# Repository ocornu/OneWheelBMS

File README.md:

# OneWheelBMS
Open source BMS for OneWheel v1/plus

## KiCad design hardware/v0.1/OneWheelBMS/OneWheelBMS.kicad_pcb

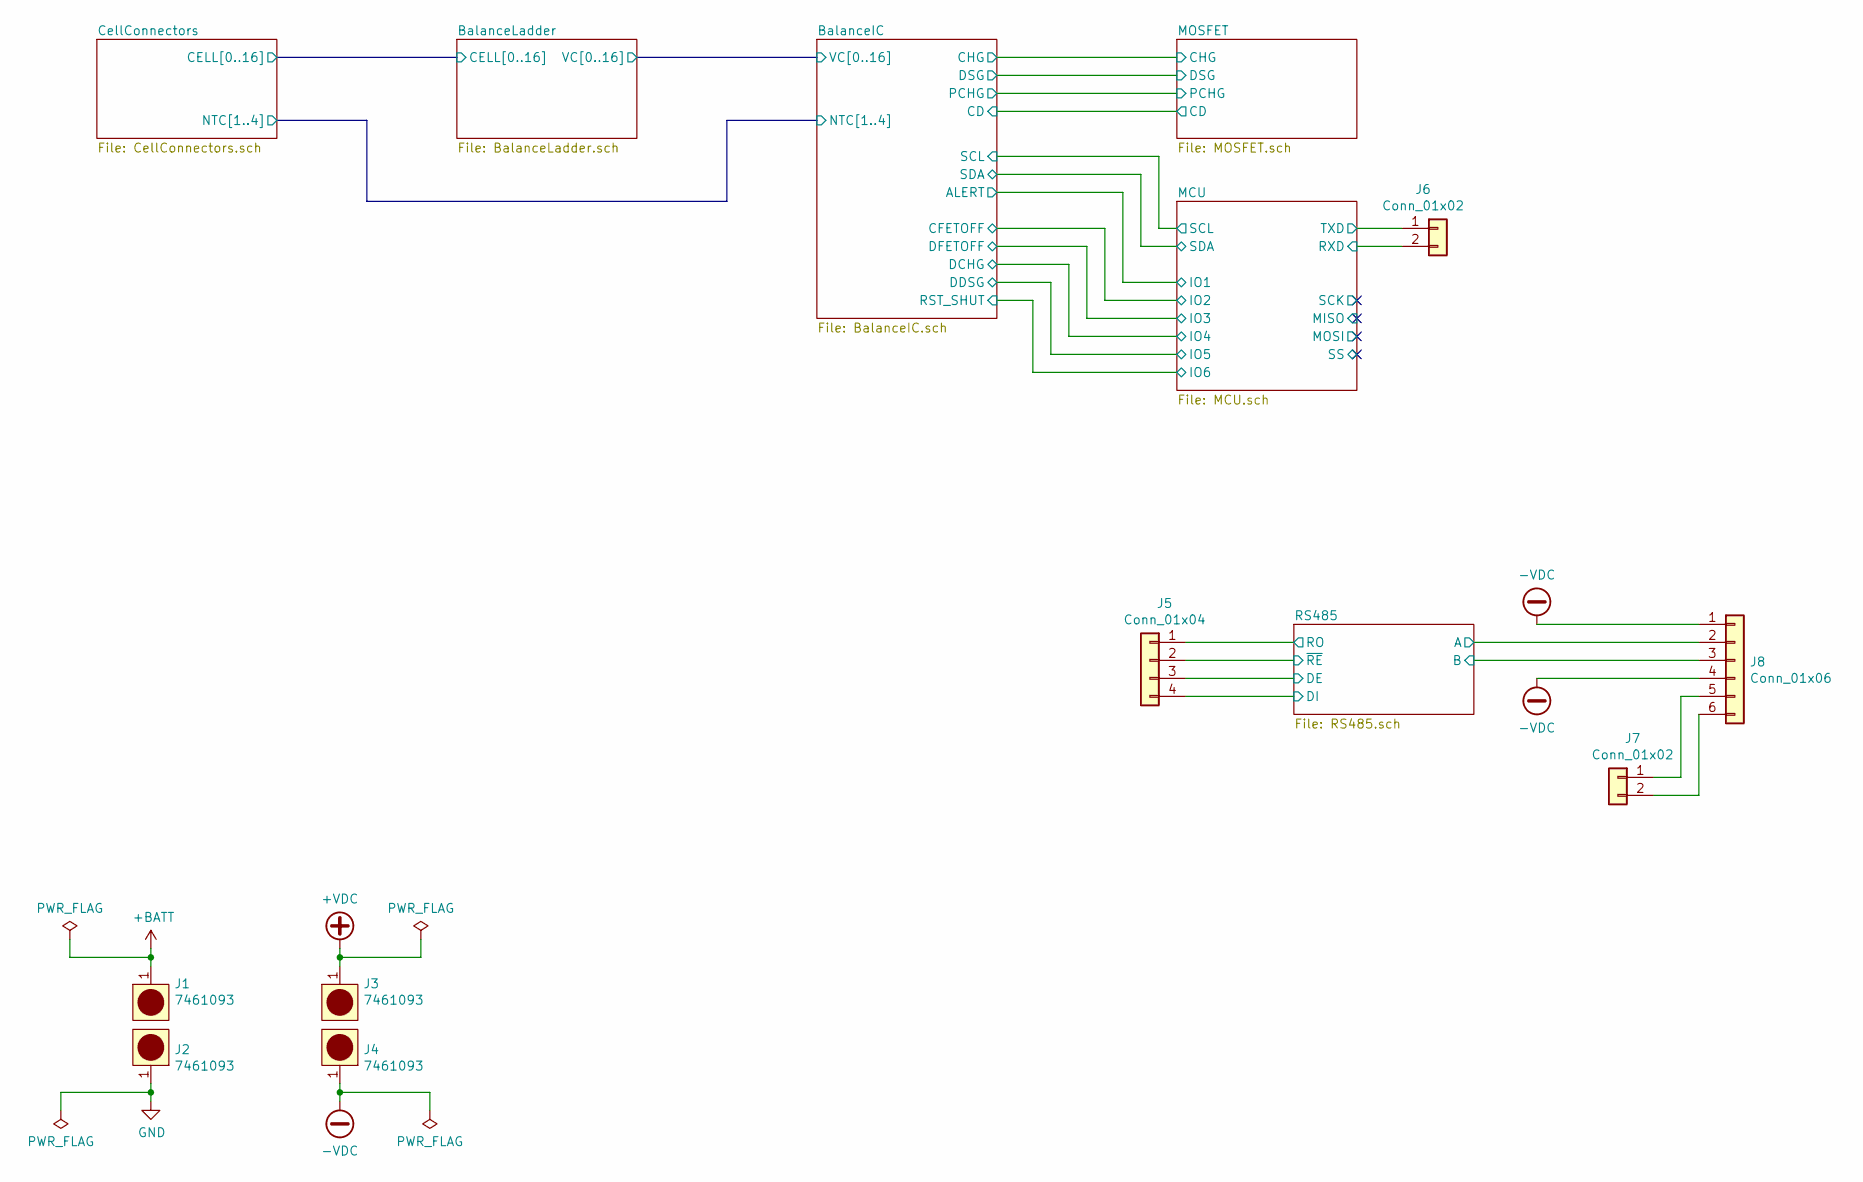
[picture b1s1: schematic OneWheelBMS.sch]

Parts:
J1, J2, J3, J4: 7461093
J5: Conn_01x04; PinHeader_1x04_P2.54mm_Vertical
J6, J7: Conn_01x02; PinHeader_1x02_P2.54mm_Vertical
J8: Conn_01x06; 5600200620

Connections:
+BATT: J1.1; also elsewhere on the board
+VDC: J3.1; also elsewhere on the board
-VDC: J4.1, J8.1, J8.4; also elsewhere on the board
/MCU/RXD: J6.2; also elsewhere on the board
/MCU/TXD: J6.1; also elsewhere on the board
/RS485/A: J8.2; also elsewhere on the board
/RS485/B: J8.3; also elsewhere on the board
/RS485/DE: J5.3; also elsewhere on the board
/RS485/DI: J5.4; also elsewhere on the board
/RS485/RO: J5.1; also elsewhere on the board
/RS485/~RE: J5.2; also elsewhere on the board
GND: J2.1; also elsewhere on the board
unnamed: J7.1, J8.5
unnamed: J7.2, J8.6

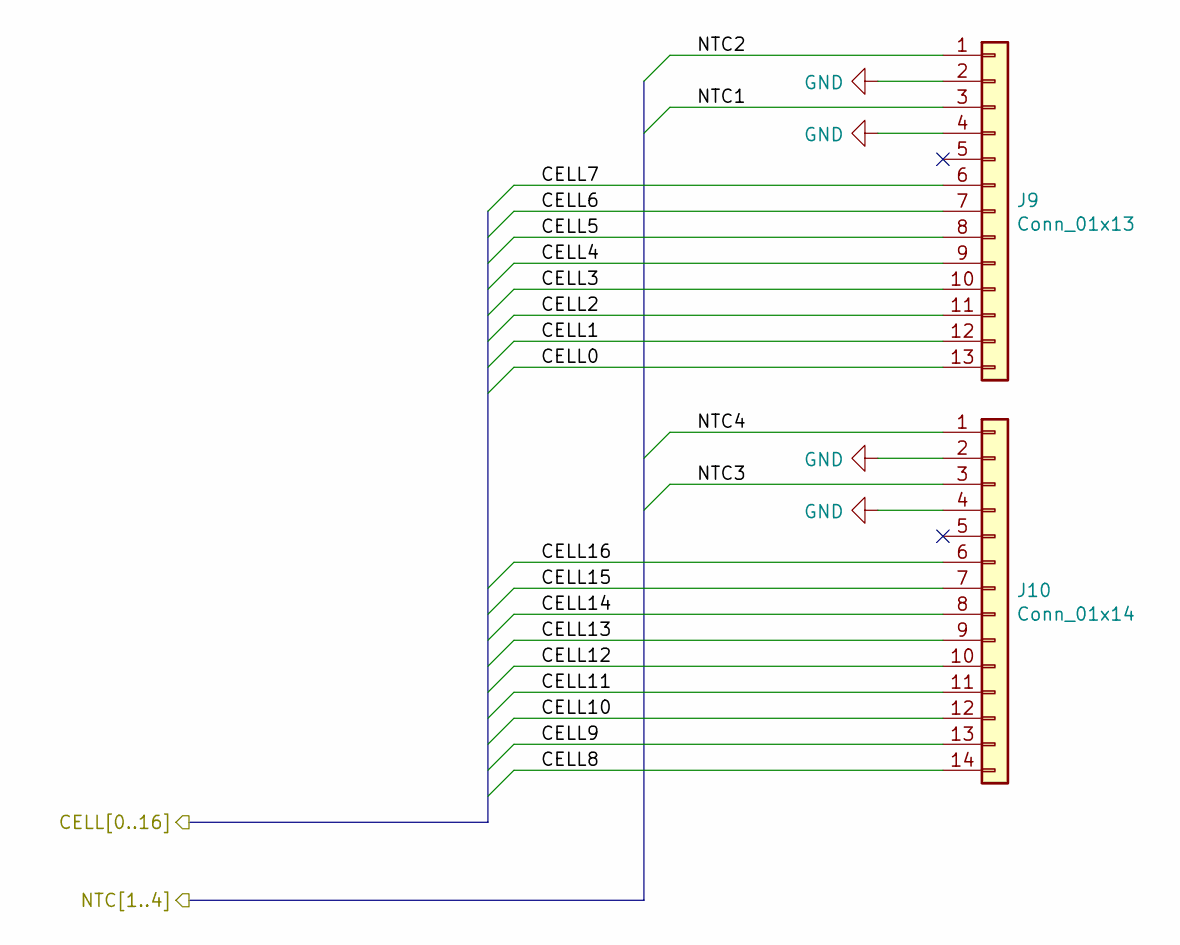
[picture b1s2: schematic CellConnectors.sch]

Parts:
J9: Conn_01x13; JST_XH_B13B-XH-A_1x13_P2.50mm_Vertical
J10: Conn_01x14; JST_XH_B14B-XH-A_1x14_P2.50mm_Vertical

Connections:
/BalanceIC/NTC1: J9.3; also elsewhere on the board
/BalanceIC/NTC2: J9.1; also elsewhere on the board
/BalanceIC/NTC3: J10.3; also elsewhere on the board
/BalanceIC/NTC4: J10.1; also elsewhere on the board
/BalanceLadder/CELL0: J9.13; also elsewhere on the board
/BalanceLadder/CELL1: J9.12; also elsewhere on the board
/BalanceLadder/CELL2: J9.11; also elsewhere on the board
/BalanceLadder/CELL3: J9.10; also elsewhere on the board
/BalanceLadder/CELL4: J9.9; also elsewhere on the board
/BalanceLadder/CELL5: J9.8; also elsewhere on the board
/BalanceLadder/CELL6: J9.7; also elsewhere on the board
/BalanceLadder/CELL7: J9.6; also elsewhere on the board
/BalanceLadder/CELL8: J10.14; also elsewhere on the board
/BalanceLadder/CELL9: J10.13; also elsewhere on the board
/BalanceLadder/CELL10: J10.12; also elsewhere on the board
/BalanceLadder/CELL11: J10.11; also elsewhere on the board
/BalanceLadder/CELL12: J10.10; also elsewhere on the board
/BalanceLadder/CELL13: J10.9; also elsewhere on the board
/BalanceLadder/CELL14: J10.8; also elsewhere on the board
/BalanceLadder/CELL15: J10.7; also elsewhere on the board
/BalanceLadder/CELL16: J10.6; also elsewhere on the board
GND: J9.2, J9.4, J10.2, J10.4; also elsewhere on the board

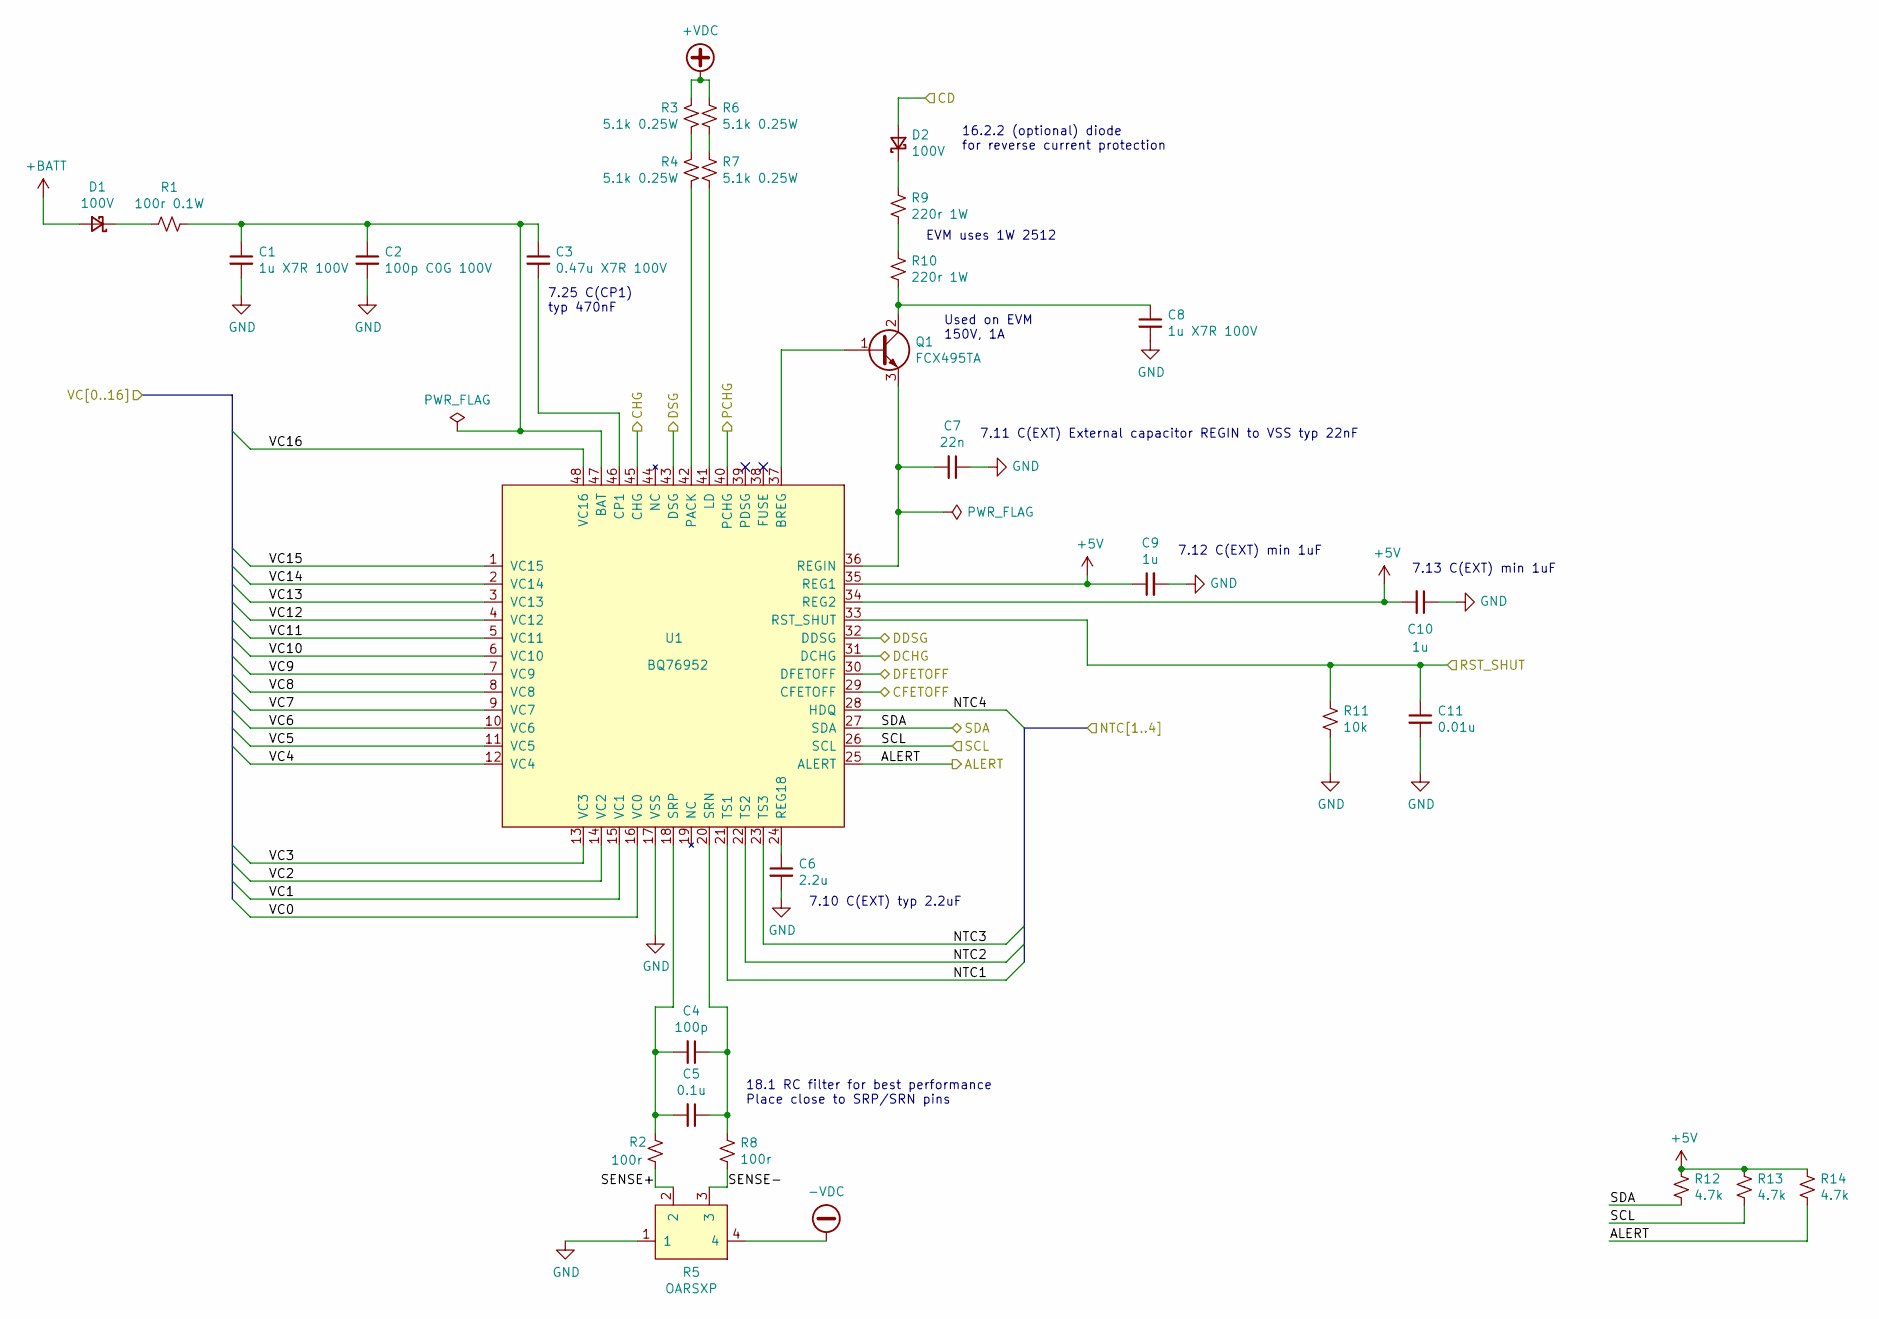
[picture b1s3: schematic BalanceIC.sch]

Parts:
C1, C8: 1u X7R 100V; C_0805_2012Metric
C2: 100p C0G 100V; C_0805_2012Metric
C3: 0.47u X7R 100V; C_0805_2012Metric
C4: 100p; C_0603_1608Metric
C5: 0.1u; C_0603_1608Metric
C6: 2.2u; C_0603_1608Metric
C7: 22n; C_0603_1608Metric
C9, C10: 1u; C_0603_1608Metric
C11: 0.01u; C_0603_1608Metric
D1, D2: 100V; D_SOD-123
Q1: FCX495TA; SOT-89-3
R1: 100r 0.1W; R_0805_2012Metric
R2, R8: 100r; R_0805_2012Metric
R3, R4, R6, R7: 5.1k 0.25W; R_0805_2012Metric
R5: OARSXP
R9, R10: 220r 1W; R_0612_1632Metric
R11: 10k; R_0603_1608Metric
R12, R13, R14: 4.7k; R_0603_1608Metric
U1: BQ76952; TQFP-48_7x7mm_P0.5mm

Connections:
+5V: C9.1, C10.2, R12.1, R13.1, R14.1, U1.34 (REG2), U1.35 (REG1); also elsewhere on the board
+BATT: D1.2 (A); also elsewhere on the board
+VDC: R3.1, R6.1; also elsewhere on the board
-VDC: R5.4; also elsewhere on the board
/BalanceIC/ALERT: R14.2, U1.25 (ALERT); also elsewhere on the board
/BalanceIC/CD: D2.2 (A); also elsewhere on the board
/BalanceIC/CFETOFF: U1.29 (CFETOFF); also elsewhere on the board
/BalanceIC/CHG: U1.45 (CHG); also elsewhere on the board
/BalanceIC/DCHG: U1.31 (DCHG); also elsewhere on the board
/BalanceIC/DDSG: U1.32 (DDSG); also elsewhere on the board
/BalanceIC/DFETOFF: U1.30 (DFETOFF); also elsewhere on the board
/BalanceIC/DSG: U1.43 (DSG); also elsewhere on the board
/BalanceIC/NTC1: U1.21 (TS1); also elsewhere on the board
/BalanceIC/NTC2: U1.22 (TS2); also elsewhere on the board
/BalanceIC/NTC3: U1.23 (TS3); also elsewhere on the board
/BalanceIC/NTC4: U1.28 (HDQ); also elsewhere on the board
/BalanceIC/PCHG: U1.40 (PCHG); also elsewhere on the board
/BalanceIC/SCL: R13.2, U1.26 (SCL); also elsewhere on the board
/BalanceIC/SDA: R12.2, U1.27 (SDA); also elsewhere on the board
/BalanceIC/SENSE+: R2.2, R5.2
/BalanceIC/SENSE-: R5.3, R8.2
/BalanceIC/VC0: U1.16 (VC0); also elsewhere on the board
/BalanceIC/VC1: U1.15 (VC1); also elsewhere on the board
/BalanceIC/VC2: U1.14 (VC2); also elsewhere on the board
/BalanceIC/VC3: U1.13 (VC3); also elsewhere on the board
/BalanceIC/VC4: U1.12 (VC4); also elsewhere on the board
/BalanceIC/VC5: U1.11 (VC5); also elsewhere on the board
/BalanceIC/VC6: U1.10 (VC6); also elsewhere on the board
/BalanceIC/VC7: U1.9 (VC7); also elsewhere on the board
/BalanceIC/VC8: U1.8 (VC8); also elsewhere on the board
/BalanceIC/VC9: U1.7 (VC9); also elsewhere on the board
/BalanceIC/VC10: U1.6 (VC10); also elsewhere on the board
/BalanceIC/VC11: U1.5 (VC11); also elsewhere on the board
/BalanceIC/VC12: U1.4 (VC12); also elsewhere on the board
/BalanceIC/VC13: U1.3 (VC13); also elsewhere on the board
/BalanceIC/VC14: U1.2 (VC14); also elsewhere on the board
/BalanceIC/VC15: U1.1 (VC15); also elsewhere on the board
/BalanceIC/VC16: U1.48 (VC16); also elsewhere on the board
/MCU/IO6: C11.1, R11.1, U1.33 (RST_SHUT); also elsewhere on the board
GND: C1.2, C2.2, C6.2, C7.1, C8.2, C9.2, C10.1, C11.2, R5.1, R11.2, U1.17 (VSS); also elsewhere on the board
unnamed: C1.1, C2.1, C3.1, R1.1, U1.47 (BAT)
unnamed: C3.2, U1.46 (CP1)
unnamed: C4.1, C5.1, R8.1, U1.20 (SRN)
unnamed: C4.2, C5.2, R2.1, U1.18 (SRP)
unnamed: C6.1, U1.24 (REG18)
unnamed: C7.2, Q1.3 (E), U1.36 (REGIN)
unnamed: C8.1, Q1.2 (C), R10.2
unnamed: D1.1 (K), R1.2
unnamed: D2.1 (K), R9.1
unnamed: Q1.1 (B), U1.37 (BREG)
unnamed: R3.2, R4.1
unnamed: R4.2, U1.42 (PACK)
unnamed: R6.2, R7.1
unnamed: R7.2, U1.41 (LD)
unnamed: R9.2, R10.1

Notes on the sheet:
7.11 C(EXT) External capacitor REGIN to VSS typ 22nF
7.12 C(EXT) min 1uF
7.13 C(EXT) min 1uF
7.10 C(EXT) typ 2.2uF
7.25 C(CP1) typ 470nF
18.1 RC filter for best performance Place close to SRP/SRN pins
16.2.2 (optional) diode for reverse current protection
Used on EVM 150V, 1A
EVM uses 1W 2512

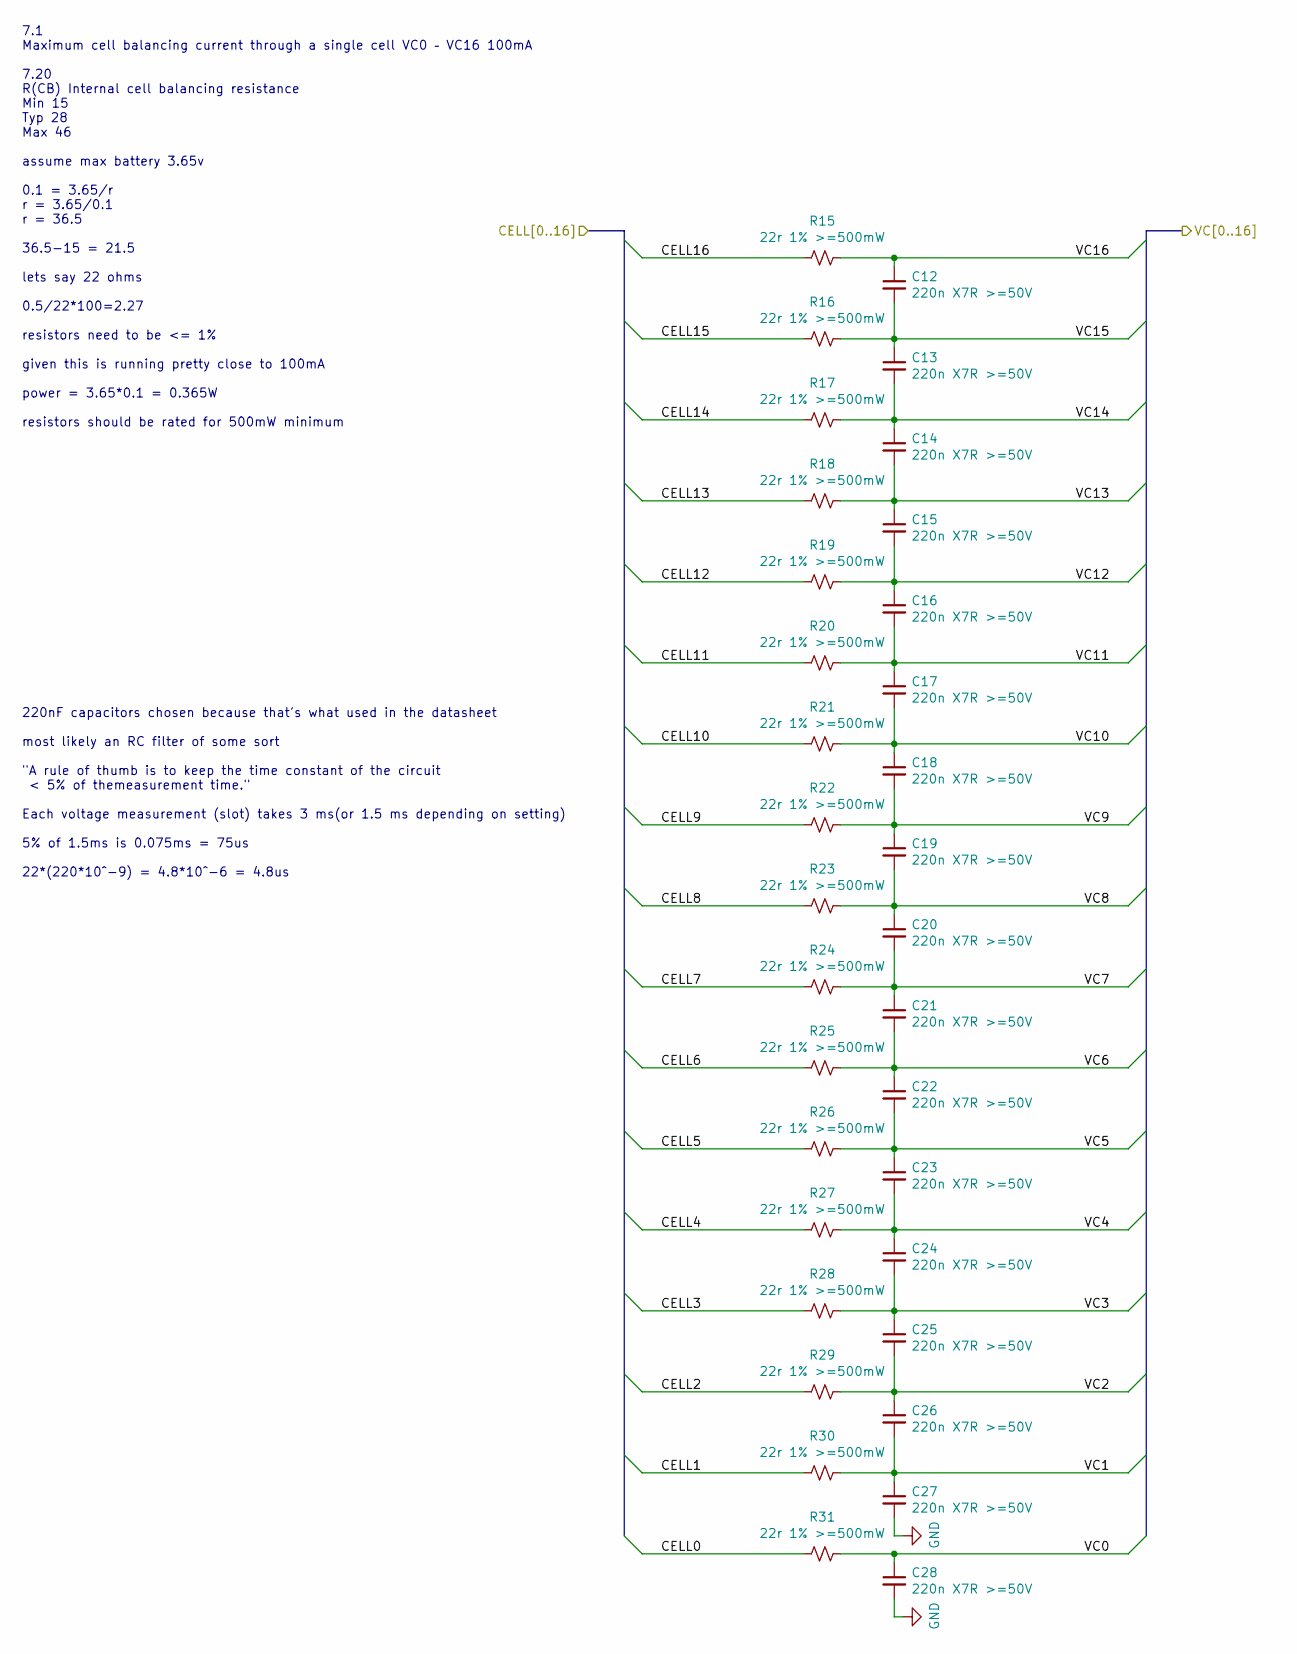
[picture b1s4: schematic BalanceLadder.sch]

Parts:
C12, C13, C14, C15, C16, C17, C18, C19, C20, C21, C22, C23, C24, C25, C26, C27, C28: 220n X7R >=50V; C_0603_1608Metric
R15, R16, R17, R18, R19, R20, R21, R22, R23, R24, R25, R26, R27, R28, R29, R30, R31: 22r 1% >=500mW; R_0612_1632Metric

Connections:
/BalanceIC/VC0: C28.1, R31.1; also elsewhere on the board
/BalanceIC/VC1: C26.2, C27.1, R30.1; also elsewhere on the board
/BalanceIC/VC2: C25.2, C26.1, R29.1; also elsewhere on the board
/BalanceIC/VC3: C24.2, C25.1, R28.1; also elsewhere on the board
/BalanceIC/VC4: C23.2, C24.1, R27.1; also elsewhere on the board
/BalanceIC/VC5: C22.2, C23.1, R26.1; also elsewhere on the board
/BalanceIC/VC6: C21.2, C22.1, R25.1; also elsewhere on the board
/BalanceIC/VC7: C20.2, C21.1, R24.1; also elsewhere on the board
/BalanceIC/VC8: C19.2, C20.1, R23.1; also elsewhere on the board
/BalanceIC/VC9: C18.2, C19.1, R22.1; also elsewhere on the board
/BalanceIC/VC10: C17.2, C18.1, R21.1; also elsewhere on the board
/BalanceIC/VC11: C16.2, C17.1, R20.1; also elsewhere on the board
/BalanceIC/VC12: C15.2, C16.1, R19.1; also elsewhere on the board
/BalanceIC/VC13: C14.2, C15.1, R18.1; also elsewhere on the board
/BalanceIC/VC14: C13.2, C14.1, R17.1; also elsewhere on the board
/BalanceIC/VC15: C12.2, C13.1, R16.1; also elsewhere on the board
/BalanceIC/VC16: C12.1, R15.1; also elsewhere on the board
/BalanceLadder/CELL0: R31.2; also elsewhere on the board
/BalanceLadder/CELL1: R30.2; also elsewhere on the board
/BalanceLadder/CELL2: R29.2; also elsewhere on the board
/BalanceLadder/CELL3: R28.2; also elsewhere on the board
/BalanceLadder/CELL4: R27.2; also elsewhere on the board
/BalanceLadder/CELL5: R26.2; also elsewhere on the board
/BalanceLadder/CELL6: R25.2; also elsewhere on the board
/BalanceLadder/CELL7: R24.2; also elsewhere on the board
/BalanceLadder/CELL8: R23.2; also elsewhere on the board
/BalanceLadder/CELL9: R22.2; also elsewhere on the board
/BalanceLadder/CELL10: R21.2; also elsewhere on the board
/BalanceLadder/CELL11: R20.2; also elsewhere on the board
/BalanceLadder/CELL12: R19.2; also elsewhere on the board
/BalanceLadder/CELL13: R18.2; also elsewhere on the board
/BalanceLadder/CELL14: R17.2; also elsewhere on the board
/BalanceLadder/CELL15: R16.2; also elsewhere on the board
/BalanceLadder/CELL16: R15.2; also elsewhere on the board
GND: C27.2, C28.2; also elsewhere on the board

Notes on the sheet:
7.1 Maximum cell balancing current through a single cell VC0 – VC16 100mA 7.20 R(CB) Internal cell balancing resistance Min 15 Typ 28 Max 46 assume max battery 3.65v 0.1 = 3.65/r r = 3.65/0.1 r = 36.5 36.5-15 = 21.5 lets say 22 ohms 0.5/22*100=2.27 resistors need to be <= 1% given this is running p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
220nF capacitors chosen because that's what used in the datasheet most likely an RC filter of some sort "A rule of thumb is to keep the time constant of the circuit < 5% of themeasurement time." Each voltage measurement (slot) takes 3 ms(or 1.5 ms depending on setting) 5% of 1.5ms is 0.075ms = 75us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

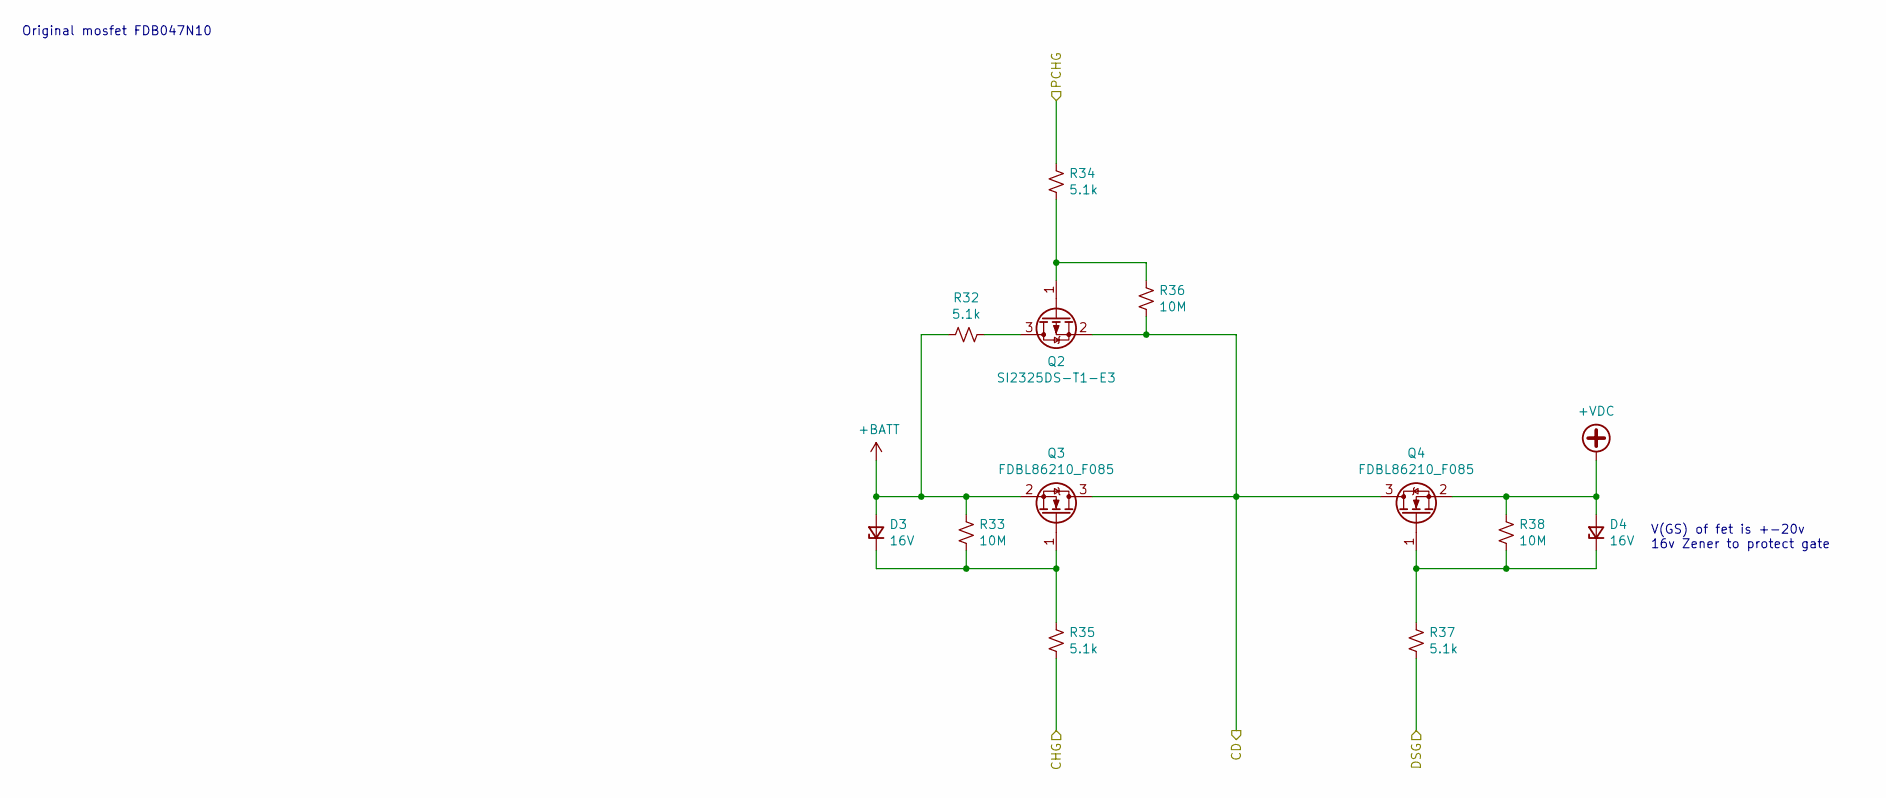
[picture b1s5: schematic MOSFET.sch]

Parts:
D3, D4: 16V; D_SOD-123
Q2: SI2325DS-T1-E3; SOT-323_SC-70
Q3, Q4: FDBL86210_F085; Infineon_PG-HSOF-8-1_ThermalVias
R32: 5.1k; R_1210_3225Metric
R33, R36, R38: 10M; R_0805_2012Metric
R34, R35, R37: 5.1k; R_0805_2012Metric

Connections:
+BATT: D3.2 (A), Q3.2 (S), R32.2, R33.1; also elsewhere on the board
+VDC: D4.2 (A), Q4.2 (S), R38.1; also elsewhere on the board
/BalanceIC/CD: Q2.2 (S), Q3.3 (D), Q4.3 (D), R36.2; also elsewhere on the board
/BalanceIC/CHG: R35.2; also elsewhere on the board
/BalanceIC/DSG: R37.2; also elsewhere on the board
/BalanceIC/PCHG: R34.1; also elsewhere on the board
unnamed: D3.1 (K), Q3.1 (G), R33.2, R35.1
unnamed: D4.1 (K), Q4.1 (G), R37.1, R38.2
unnamed: Q2.1 (G), R34.2, R36.1
unnamed: Q2.3 (D), R32.1

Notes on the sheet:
V(GS) of fet is +-20v 16v Zener to protect gate
Original mosfet FDB047N10

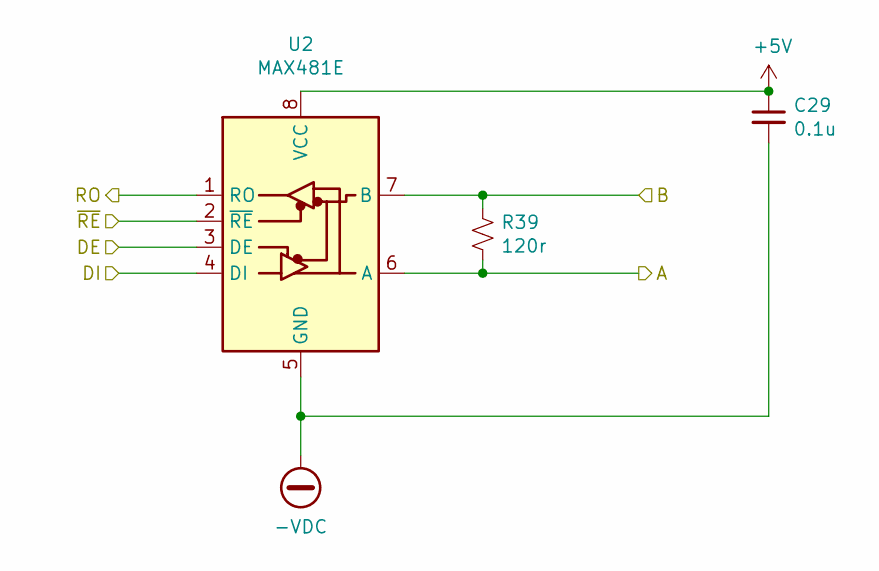
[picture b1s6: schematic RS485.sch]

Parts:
C29: 0.1u; C_0603_1608Metric
R39: 120r; R_0603_1608Metric
U2: MAX481E; SO-8_3.9x4.9mm_P1.27mm

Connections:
+5V: C29.1, U2.8 (VCC); also elsewhere on the board
-VDC: C29.2, U2.5 (GND); also elsewhere on the board
/RS485/A: R39.2, U2.6 (A); also elsewhere on the board
/RS485/B: R39.1, U2.7 (B); also elsewhere on the board
/RS485/DE: U2.3 (DE); also elsewhere on the board
/RS485/DI: U2.4 (DI); also elsewhere on the board
/RS485/RO: U2.1 (RO); also elsewhere on the board
/RS485/~RE: U2.2 (~RE); also elsewhere on the board

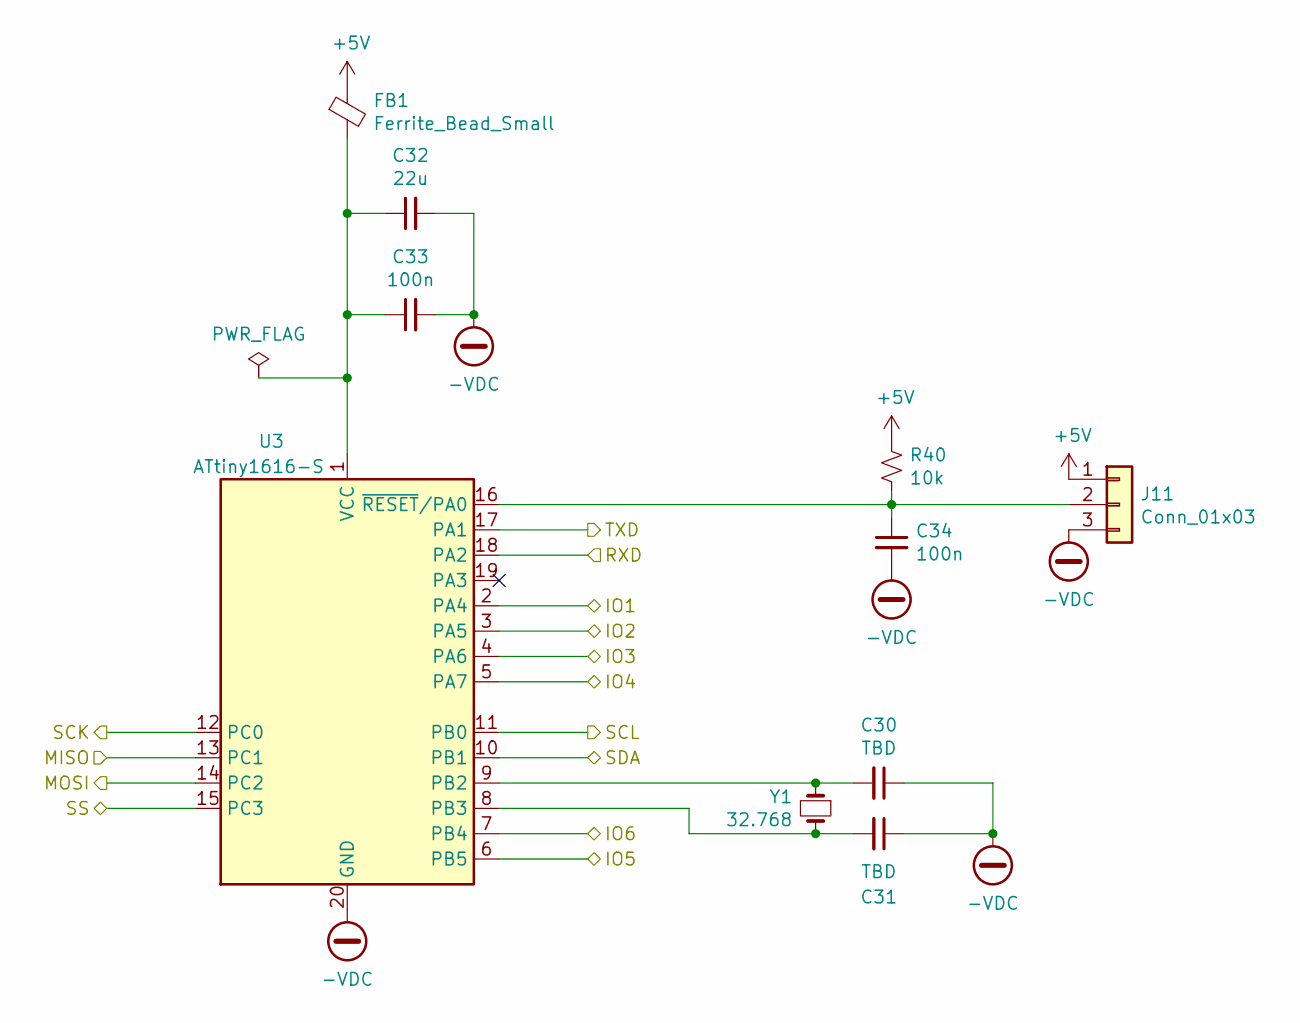
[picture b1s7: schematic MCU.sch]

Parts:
C30, C31: TBD; C_0603_1608Metric
C32: 22u; C_1206_3216Metric
C33, C34: 100n; C_0603_1608Metric
FB1: Ferrite_Bead_Small; L_0805_2012Metric
J11: Conn_01x03; PinHeader_1x03_P2.54mm_Vertical
R40: 10k; R_0603_1608Metric
U3: ATtiny1616-S; SOIC-20W_7.5x12.8mm_P1.27mm
Y1: 32.768; Crystal_SMD_3215-2Pin_3.2x1.5mm

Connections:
+5V: FB1.1, J11.1, R40.1; also elsewhere on the board
-VDC: C30.1, C31.1, C32.2, C33.2, C34.2, J11.3, U3.20 (GND); also elsewhere on the board
/BalanceIC/ALERT: U3.2 (PA4); also elsewhere on the board
/BalanceIC/CFETOFF: U3.3 (PA5); also elsewhere on the board
/BalanceIC/DCHG: U3.5 (PA7); also elsewhere on the board
/BalanceIC/DDSG: U3.6 (PB5); also elsewhere on the board
/BalanceIC/DFETOFF: U3.4 (PA6); also elsewhere on the board
/BalanceIC/SCL: U3.11 (PB0); also elsewhere on the board
/BalanceIC/SDA: U3.10 (PB1); also elsewhere on the board
/MCU/IO6: U3.7 (PB4); also elsewhere on the board
/MCU/MISO: U3.13 (PC1)
/MCU/MOSI: U3.14 (PC2)
/MCU/RXD: U3.18 (PA2); also elsewhere on the board
/MCU/SCK: U3.12 (PC0)
/MCU/SS: U3.15 (PC3)
/MCU/TXD: U3.17 (PA1); also elsewhere on the board
unnamed: C30.2, U3.9 (PB2), Y1.1
unnamed: C31.2, U3.8 (PB3), Y1.2
unnamed: C32.1, C33.1, FB1.2, U3.1 (VCC)
unnamed: C34.1, J11.2, R40.2, U3.16 (~RESET~/PA0)

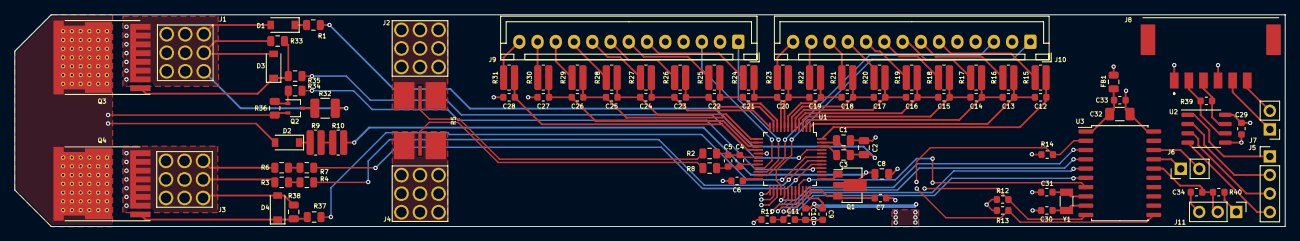
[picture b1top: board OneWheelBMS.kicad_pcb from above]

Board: 4 copper layers, 174.0 x 29.0 mm, 98 parts (0 on the bottom side), 90 nets.

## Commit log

2020-10-20 Initial hardware commit
